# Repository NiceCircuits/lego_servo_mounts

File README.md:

lego_servo_mounts
=================

Some dirty 3D models of servo to lego adapters etc.

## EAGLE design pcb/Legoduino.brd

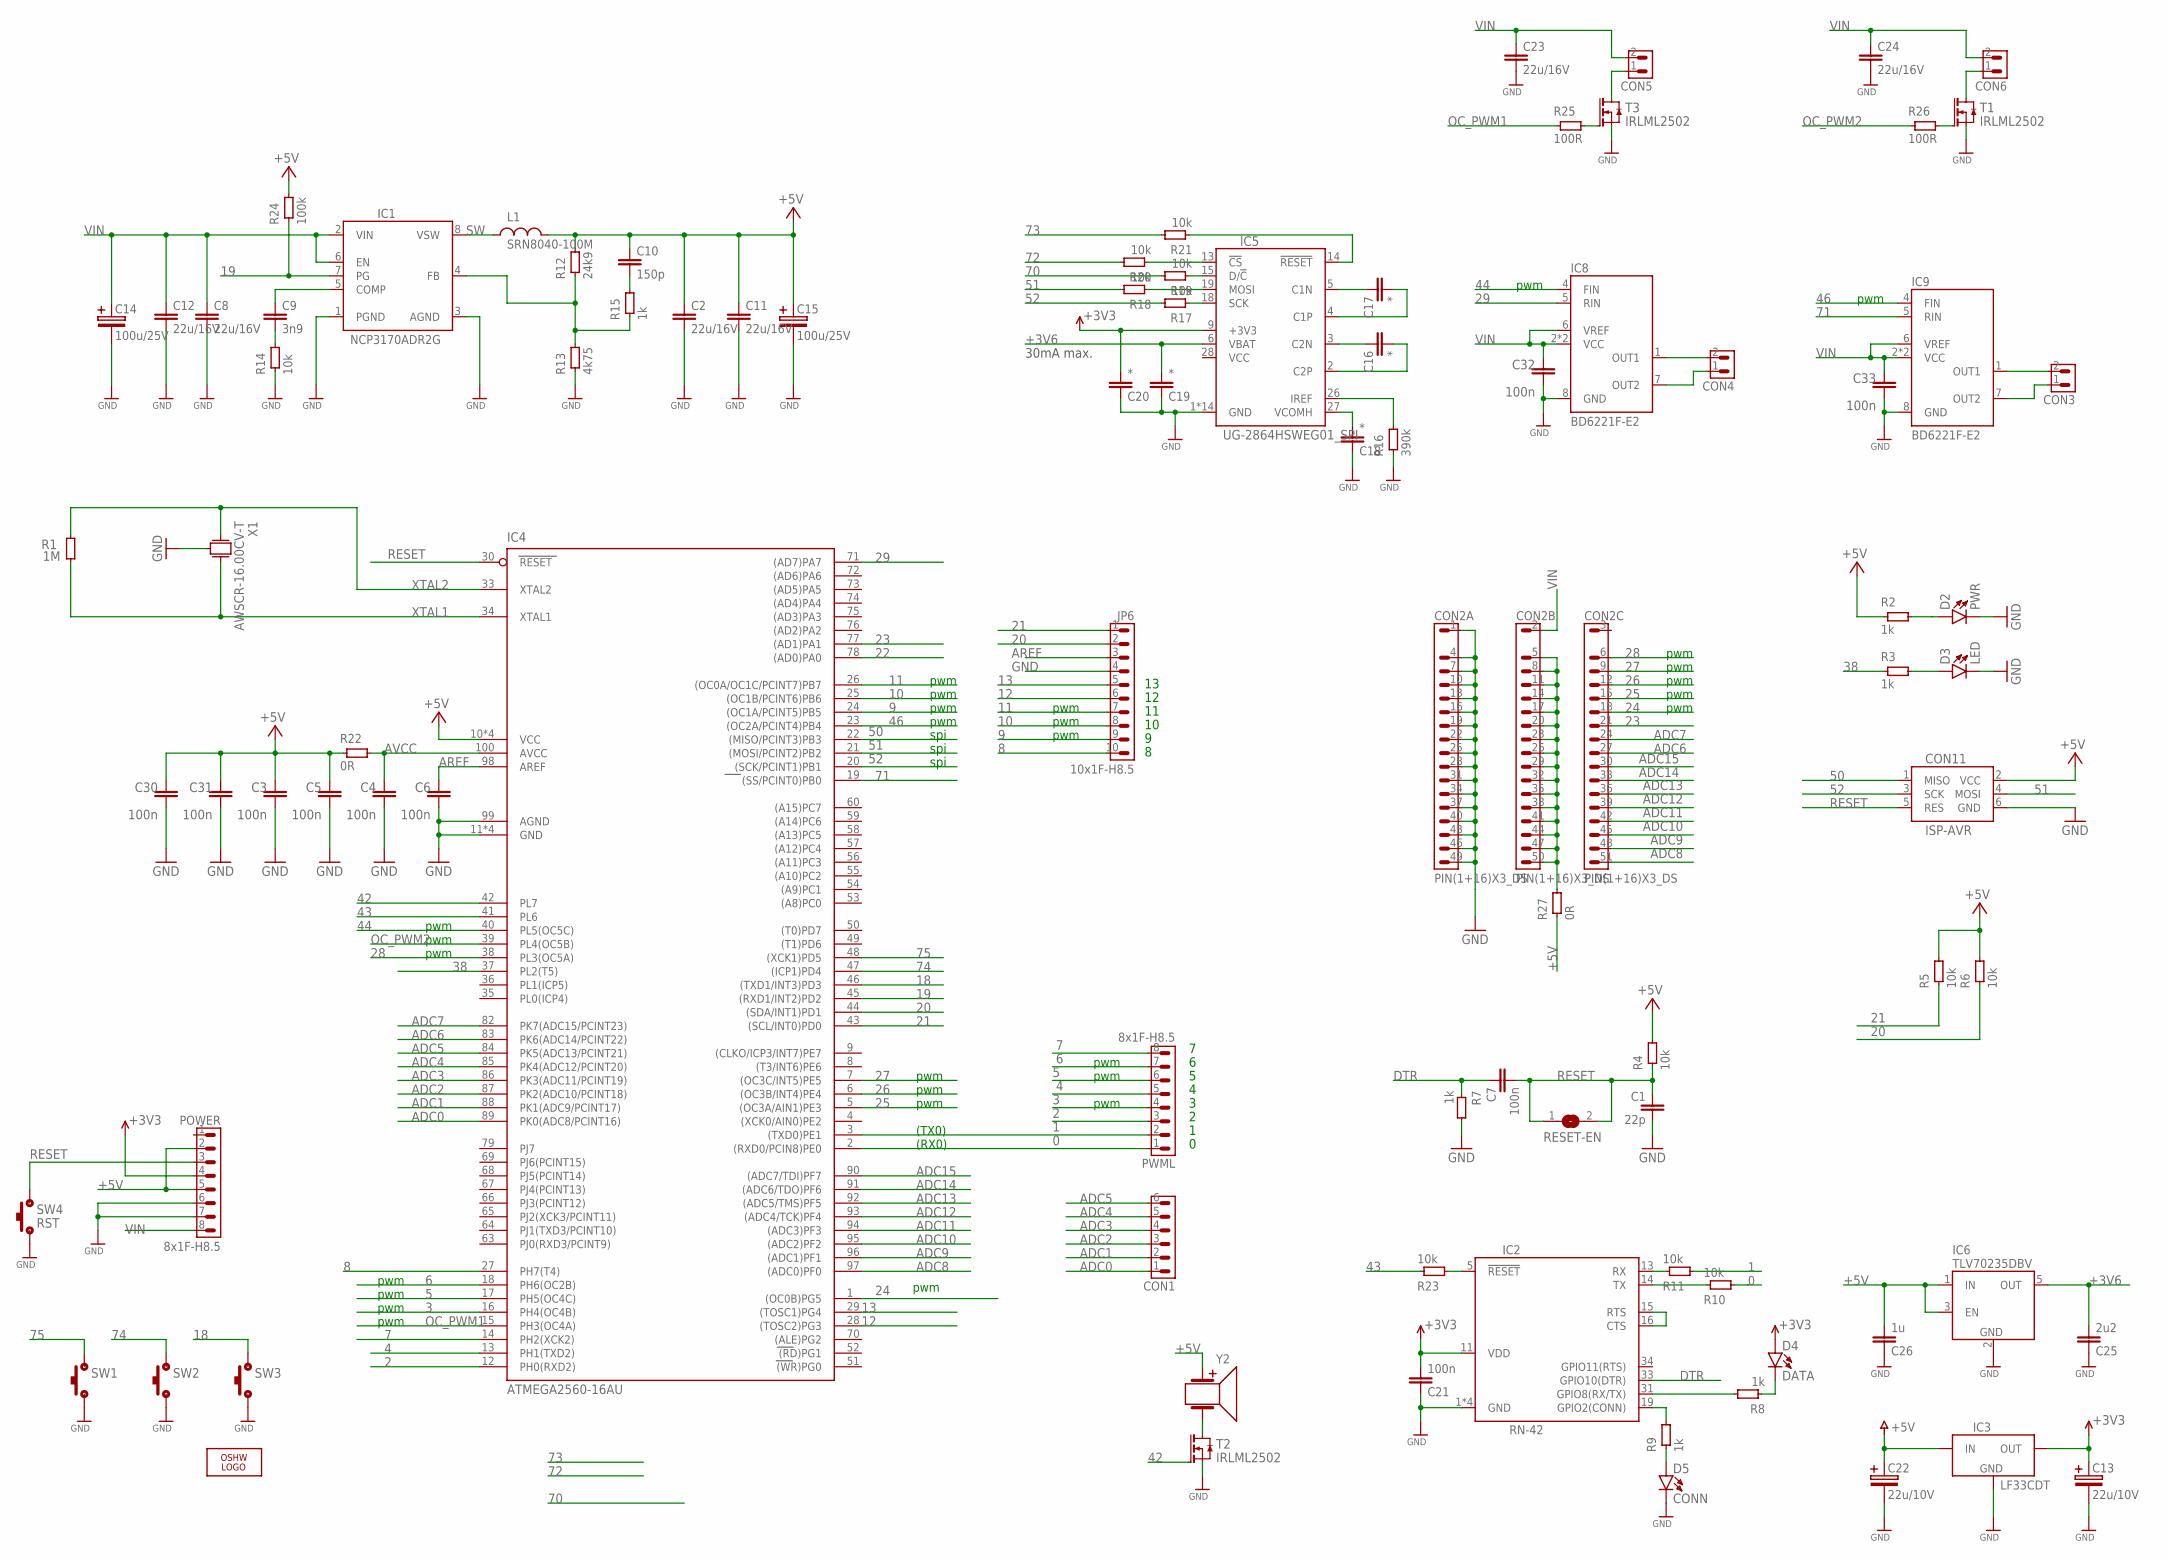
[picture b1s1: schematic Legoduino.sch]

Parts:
C1: 22p; 0603
C2, C8, C11, C12, C23, C24: 22u/16V; 1210
C3, C4, C5, C6, C7, C21, C30, C31, C32, C33: 100n; 0603
C9: 3n9; 0603
C10: 150p; 0603
C13, C22: 22u/10V; SMC_A
C14, C15: 100u/25V; CE_SMD6.3
C16, C17, C18, C19, C20: *; 0603
C25: 2u2; 0603
C26: 1u; 0603
CON1: PIN6X1C
CON2: PIN(1+16)X3_DS
CON3, CON4, CON5, CON6: PIN2X1C
CON11: ISP-AVR; PIN3X2
D2: PWR; D0805
D3: LED; D0805
D4: DATA; D0805
D5: CONN; D0805
IC1: NCP3170ADR2G; SO08
IC2: RN-42; RN42
IC3: LF33CDT; DPAK
IC4: ATMEGA2560-16AU; TQFP100
IC5: UG-2864HSWEG01_SPI; UG-2864HSWEG01
IC6: TLV70235DBV; SOT23-5
IC8, IC9: BD6221F-E2; SO08
JP6: 10x1F-H8.5; PIN10X1C
L1: SRN8040-100M; SRN8040
LOGO1: OSHW_LOGO_10MILX0200-NT; OSHW_10X200_NOTEXT
POWER: 8x1F-H8.5; PIN8X1C
PWML: 8x1F-H8.5; PIN8X1C
R1: 1M; 0603
R2, R3, R7, R8, R9, R15: 1k; 0603
R4, R5, R6, R10, R11, R14, R17, R18, R19, R20, R21, R23: 10k; 0603
R12: 24k9; 0603
R13: 4k75; 0603
R16: 390k; 0603
R22: 0R; 0603
R24: 100k; 0603
R25, R26: 100R; 0603
R27: 0R; 0805
RESET-EN: SJ
SW1, SW2, SW3: SW_SMD; MICROSW_SMD
SW4: RST; MICROSW_SMD
T1, T2, T3: IRLML2502; SOT23
X1: AWSCR-16.00CV-T; CERAMIC_3.7X3.1
Y2: BUZZER-HCM

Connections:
0: IC4.2 ((RXD0/PCIN8)PE0), PWML.1, R10.2
1: IC4.3 ((TXD0)PE1), PWML.2, R11.2
2: IC4.12 (PH0(RXD2)), PWML.3
3: IC4.16 (PH4(OC4B)), PWML.4
4: IC4.13 (PH1(TXD2)), PWML.5
5: IC4.17 (PH5(OC4C)), PWML.6
6: IC4.18 (PH6(OC2B)), PWML.7
7: IC4.14 (PH2(XCK2)), PWML.8
8: IC4.27 (PH7(T4)), JP6.10
9: IC4.24 ((OC1A/PCINT5)PB5), JP6.9
10: IC4.25 ((OC1B/PCINT6)PB6), JP6.8
11: IC4.26 ((OC0A/OC1C/PCINT7)PB7), JP6.7
12: IC4.28 ((TOSC2)PG3), JP6.6
13: IC4.29 ((TOSC1)PG4), JP6.5
18: IC4.46 ((TXD1/INT3)PD3), SW3.1, SW3.1A (1)
19: IC1.7 (PG), IC4.45 ((RXD1/INT2)PD2), R24.1
20: IC4.44 ((SDA/INT1)PD1), JP6.2, R6.1
21: IC4.43 ((SCL/INT0)PD0), JP6.1, R5.1
22: IC4.78 ((AD0)PA0)
23: CON2.21 (7), IC4.77 ((AD1)PA1)
24: CON2.18 (6), IC4.1 ((OC0B)PG5)
25: CON2.15 (5), IC4.5 ((OC3A/AIN1)PE3)
26: CON2.12 (4), IC4.6 ((OC3B/INT4)PE4)
27: CON2.9 (3), IC4.7 ((OC3C/INT5)PE5)
28: CON2.6 (2), IC4.38 (PL3(OC5A))
29: IC4.71 ((AD7)PA7), IC8.5 (RIN)
38: IC4.37 (PL2(T5)), R3.1
42: IC4.42 (PL7), T2.1 (G)
43: IC4.41 (PL6), R23.1
44: IC4.40 (PL5(OC5C)), IC8.4 (FIN)
46: IC4.23 ((OC2A/PCINT4)PB4), IC9.4 (FIN)
50: CON11.1 (MISO), IC4.22 ((MISO/PCINT3)PB3)
51: CON11.4 (MOSI), IC4.21 ((MOSI/PCINT2)PB2), R18.2
52: CON11.3 (SCK), IC4.20 ((SCK/PCINT1)PB1), R17.2
70: R19.2
71: IC4.19 ((SS/PCINT0)PB0), IC9.5 (RIN)
72: R20.2
73: R21.2
74: IC4.47 ((ICP1)PD4), SW2.1, SW2.1A (1)
75: IC4.48 ((XCK1)PD5), SW1.1, SW1.1A (1)
+3V3: C13.+, C20.2, C21.2, D4.A, IC2.11 (VDD), IC3.3 (OUT), IC5.9 (+3V3), POWER.4
+3V6: C19.2, C25.2, IC5.6 (VBAT), IC6.5 (OUT)
+5V: C2.1, C3.1, C5.1, C10.1, C11.1, C15.+, C22.+, C26.2, C30.1, C31.1, CON11.2 (VCC), IC3.1 (IN), IC4.10 (VCC), IC4.31 (VCC), IC4.61 (VCC), IC4.80 (VCC), IC6.1 (IN), IC6.3 (EN), L1.2, POWER.2, POWER.5, R2.1, R4.2, R5.2, R6.2, R12.2, R22.1, R24.2, R27.1, Y2.+
+5VP_O: CON2.5 (2), CON2.8 (3), CON2.11 (4), CON2.14 (5), CON2.17 (6), CON2.20 (7), CON2.23 (8), CON2.26 (9), CON2.29 (10), CON2.32 (11), CON2.35 (12), CON2.38 (13), CON2.41 (14), CON2.44 (15), CON2.47 (16), CON2.50 (17), R27.2
ADC0: CON1.1, IC4.89 (PK0(ADC8/PCINT16))
ADC1: CON1.2, IC4.88 (PK1(ADC9/PCINT17))
ADC2: CON1.3, IC4.87 (PK2(ADC10/PCINT18))
ADC3: CON1.4, IC4.86 (PK3(ADC11/PCINT19))
ADC4: CON1.5, IC4.85 (PK4(ADC12/PCINT20))
ADC5: CON1.6, IC4.84 (PK5(ADC13/PCINT21))
ADC6: CON2.27 (9), IC4.83 (PK6(ADC14/PCINT22))
ADC7: CON2.24 (8), IC4.82 (PK7(ADC15/PCINT23))
ADC8: CON2.51 (17), IC4.97 ((ADC0)PF0)
ADC9: CON2.48 (16), IC4.96 ((ADC1)PF1)
ADC10: CON2.45 (15), IC4.95 ((ADC2)PF2)
ADC11: CON2.42 (14), IC4.94 ((ADC3)PF3)
ADC12: CON2.39 (13), IC4.93 ((ADC4/TCK)PF4)
ADC13: CON2.36 (12), IC4.92 ((ADC5/TMS)PF5)
ADC14: CON2.33 (11), IC4.91 ((ADC6/TDO)PF6)
ADC15: CON2.30 (10), IC4.90 ((ADC7/TDI)PF7)
AREF: C6.1, IC4.98 (AREF), JP6.3
AVCC: C4.1, IC4.100 (AVCC), R22.2
DTR: C7.1, IC2.33 (GPIO10(DTR)), R7.1
GND: C1.2, C2.2, C3.2, C4.2, C5.2, C6.2, C8.2, C11.2, C12.2, C13.-, C14.-, C15.-, C18.1, C19.1, C20.1, C21.1, C22.-, C23.2, C24.2, C25.1, C26.1, C30.2, C31.2, C32.2, C33.2, CON2.1, CON2.4 (2), CON2.7 (3), CON2.10 (4), CON2.13 (5), CON2.16 (6), CON2.19 (7), CON2.22 (8), CON2.25 (9), CON2.28 (10), CON2.31 (11), CON2.34 (12), CON2.37 (13), CON2.40 (14), CON2.43 (15), CON2.46 (16), CON2.49 (17), CON11.6 (GND), D2.K, D3.K, D5.K, IC1.1 (PGND), IC1.3 (AGND), IC2.1 (GND), IC2.12 (GND), IC2.28 (GND), IC2.29 (GND), IC3.2 (GND), IC4.11 (GND), IC4.32 (GND), IC4.62 (GND), IC4.81 (GND), IC4.99 (AGND), IC5.1 (GND), IC5.8 (GND), IC5.10 (GND), IC5.11 (GND), IC5.12 (GND), IC5.16 (GND), IC5.17 (GND), IC5.21 (GND), IC5.22 (GND), IC5.23 (GND), IC5.24 (GND), IC5.25 (GND), IC5.29 (GND), IC5.30 (GND), IC6.2 (GND), IC8.8 (GND), IC9.8 (GND), JP6.4, POWER.6, POWER.7, R7.2, R13.1, R14.1, R16.1, SW1.2, SW1.2A (2), SW2.2, SW2.2A (2), SW3.2, SW3.2A (2), SW4.2, SW4.2A (2), T1.2 (S), T2.2 (S), T3.2 (S), X1.0
GND1: IC1.4 (FB), R12.1, R13.2, R15.1
unnamed: IC2.14 (TX), R10.1
unnamed: D3.A, R3.2
unnamed: D2.A, R2.2
unnamed: IC2.13 (RX), R11.1
unnamed: IC2.31 (GPIO8(RX/TX)), R8.2
unnamed: D4.K, R8.1
unnamed: D5.A, R9.1
unnamed: IC2.19 (GPIO2(CONN)), R9.2
unnamed: C18.2, IC5.27 (VCOMH)
unnamed: C9.1, IC1.5 (COMP)
unnamed: C9.2, R14.2
unnamed: IC5.26 (IREF), R16.2
unnamed: C10.2, R15.2
unnamed: C16.1, IC5.3 (C2N)
unnamed: C17.2, IC5.4 (C1P)
unnamed: C16.2, IC5.2 (C2P)
unnamed: C17.1, IC5.5 (C1N)
unnamed: IC5.13 (!CS), R20.1
unnamed: IC5.15 (D/!C), R19.1
unnamed: IC5.18 (SCK), R17.1
unnamed: IC5.19 (MOSI), R18.1
unnamed: IC2.15 (RTS), IC2.16 (CTS)
unnamed: IC5.14 (!RESET), R21.1
unnamed: R25.2, T3.1 (G)
unnamed: T2.3 (D), Y2.-
unnamed: CON5.1, T3.3 (D)
unnamed: IC2.5 (!RESET), R23.2
unnamed: R26.2, T1.1 (G)
unnamed: CON3.2, IC9.1 (OUT1)
unnamed: CON4.2, IC8.1 (OUT1)
unnamed: CON6.1, T1.3 (D)
unnamed: CON3.1, IC9.7 (OUT2)
unnamed: CON4.1, IC8.7 (OUT2)
OC_PWM1: IC4.15 (PH3(OC4A)), R25.1
OC_PWM2: IC4.39 (PL4(OC5B)), R26.1
RESET: C1.1, C7.2, CON11.5 (RES), IC4.30 (RESET), POWER.3, R4.1, RESET-EN.1, RESET-EN.2, SW4.1, SW4.1A (1)
SW: IC1.8 (VSW), L1.1
VCC: IC5.28 (VCC)
VIN: C8.1, C12.1, C14.+, C23.1, C24.1, C32.1, C33.1, CON2.2 (1), CON5.2, CON6.2, IC1.2 (VIN), IC1.6 (EN), IC8.2 (VCC), IC8.3 (VCC), IC8.6 (VREF), IC9.2 (VCC), IC9.3 (VCC), IC9.6 (VREF), POWER.8
XTAL1: IC4.34 (XTAL1), R1.1, X1.2
XTAL2: IC4.33 (XTAL2), R1.2, X1.1

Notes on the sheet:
pwm
(TX0)
(RX0)
spi
30mA max.

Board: 2 copper layers, 91 parts (10 on the bottom side), 101 nets, no tracks yet.

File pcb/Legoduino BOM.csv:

Qty;Value;Device;Package;Parts;Description
1;;BUZZER-HCM;BUZZER-HCM;Y2;
1;;NPN-SOT23;SOT23;T1;
2;;PIN2X1B;PIN2X1B;CON3, CON4;
1;;PIN6X1C;PIN6X1C;CON1;
1;;SJ;SJ;RESET-EN;SMD solder JUMPER
3;;SW_SMD;MICROSW_SMD;SW1, SW2, SW3;
6;*;C0603;603;C10, C16, C17, C18, C19, C20;
1;*;R0603;603;R15;
1;0R;R0603;603;R22;
1;0R;R0805;805;R27;
1;100k;R0603;603;R24;
10;100n;C0603;603;C3, C4, C5, C6, C7, C21, C30, C31, C32, C33;
2;100u/25V;CE_SMD6.3;CE_SMD6.3;C14, C15;kondensator elektrolityczny
13;10k;R0603;603;R4, R5, R6, R10, R11, R14, R17, R18, R19, R20, R21, R23, R26;
1;10x1F-H8.5;PIN10X1C;PIN10X1C;JP6;
1;1M;R0603;603;R1;
5;1k;R0603;603;R2, R3, R7, R8, R9;
3;1u;C0603;603;C23, C26, C29;
1;22p;C0603;603;C1;
4;22u;C1206;1206;C2, C8, C11, C12;
1;24k9;R0603;603;R12;
3;2u2;C0603;603;C22, C25, C28;
1;3n9;C0603;603;C9;
3;470p;C0603;603;C13, C24, C27;
1;4k75;R0603;603;R13;
1;560k;R0603;603;R16;
2;8x1F-H8.5;PIN8X1C;PIN8X1C;POWER, PWML;
1;ATMEGA2560-16AU;ATMEGA2560-16AU;TQFP100;IC4;MICROCONTROLLER
2;BD6221F-E2;BD6221F-E2;SO08;IC8, IC9;
1;CONN;LED0805;D0805;D5;
1;CSTCE16M0V53-R0 16MHZ;RESONATORMU;RESONATOR;Y1;
1;DATA;LED0805;D0805;D4;
1;ISP-AVR;ISP-AVR;PIN3X2;CON11;
1;LED;LED0805;D0805;D3;
1;MIC5205-3.3YM5;MIC5205-3.3YM5;SOT23-5;IC7;LDO
1;MIC5205-3.6YM5;MIC5205-3.6YM5;SOT23-5;IC6;LDO
1;MIC5205-5.0YM5;MIC5205-5.0YM5;SOT23-5;IC3;LDO
;;;;;
1;NCP3170ADR2G;NCP3170ADR2G;SO08;IC1;
;;;;;
1;PIN(1+16)X3_DS;PIN(1+16)X3_DS;PIN(1+16)X3_DS;CON2;
1;PWR;LED0805;D0805;D2;
1;RN-42;RN-42;RN42;IC2;
1;RST;SW_SMD;MICROSW_SMD;SW4;
1;SRN8040-100M;SRN8040-100M;SRN8040;L1;
1;UG-2864HSWEG01_SPI;UG-2864HSWEG01_SPI;UG-2864HSWEG01;IC5;

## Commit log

2013-08-30 Initial commit of first version of the board
2013-09-01 Working on mount for HK15148 servo
2013-09-07 File rename
2013-09-07 Modification of servo mount
2013-09-10 repair of mesh
2013-09-20 Added servo mount for MG90S- initial commit
2013-10-06 Updated feedback compensation circuit for NCP3170
2013-10-06 Updated net names according to Arduino Mega pin numbers
2013-10-12 Added test files for arduino
2013-10-12 #26 Added test firmware for motor drivers. It works fine by now. Motor driving is quite complicated: - pwm should be 20k-100kHz - we must override default TIMER5 prescalers - when running forward, pw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
2013-10-13 #28 Oled works good. Using Adafruit libraries: https://github.com/adafruit/Adafruit-GFX-Library https://github.com/adafruit/Adafruit_SSD1306
2013-10-15 Removed traces and planes from bluetooth module antenna. Closes #1
2013-10-15 R16 -> 390k. Closes #32.
2013-10-15 Reverse DATA LED polarisation. Closes #15.
2013-11-15 #20: Optimized pin assignment on arduino shield connector. PWM signals are now connected only to this lines, where PWM are on Arduino Uno board. 4 additional PWM are now connected to expansion connec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
2013-11-15 #20: Optimized pin assignment and component placement
2014-02-06 Removed unnecessary files.
2014-02-06 Removed files from v1.0. Starting development of v2.0.
2014-02-08 Extracted servo mounts from legoduino repository. Cleaning unnecessary files.
2016-01-03 Refactor
2016-01-12 New arm model
2016-01-12 Update support settings
